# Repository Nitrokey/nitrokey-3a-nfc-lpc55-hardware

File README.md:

# Nitrokey 3A NFC Hardware

The hardware files of [Nitrokey 3A NFC](https://shop.nitrokey.com/shop/nk3an-nitrokey-3a-nfc-147).
The firmware is [here](https://github.com/Nitrokey/nitrokey-3-firmware).

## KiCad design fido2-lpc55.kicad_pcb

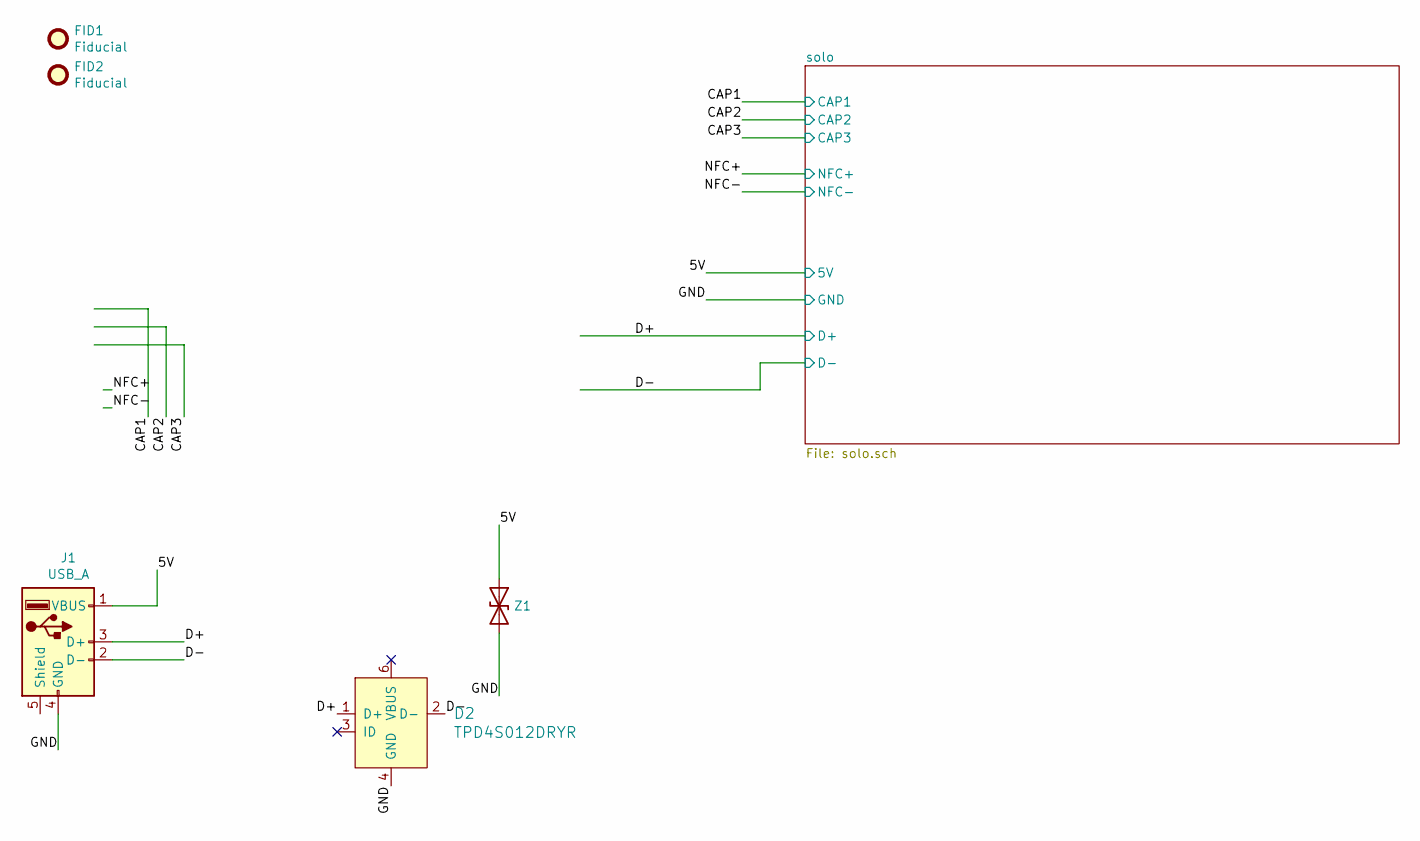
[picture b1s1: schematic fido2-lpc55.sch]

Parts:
D2: TPD4S012DRYR; UFDFN-6_1.45x1mm; MPN TPD4S012DRYR; Digi-Key_PN 296-24244-1-ND
FID1, FID2: Fiducial; Fiducial_0.5mm_Mask1mm
J1: USB_A; USB-A-PLUG
Z1: GG040205100N2P; R_0402_1005Metric; MPN GG040205100N2P

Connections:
/5V: J1.1 (VBUS), Z1.1 (A1); also elsewhere on the board
/D+: D2.1 (D+), J1.3 (D+); also elsewhere on the board
/D-: D2.2 (D-), J1.2 (D-); also elsewhere on the board
GNDREF: D2.4 (GND), J1.4 (GND), Z1.2 (A2); also elsewhere on the board

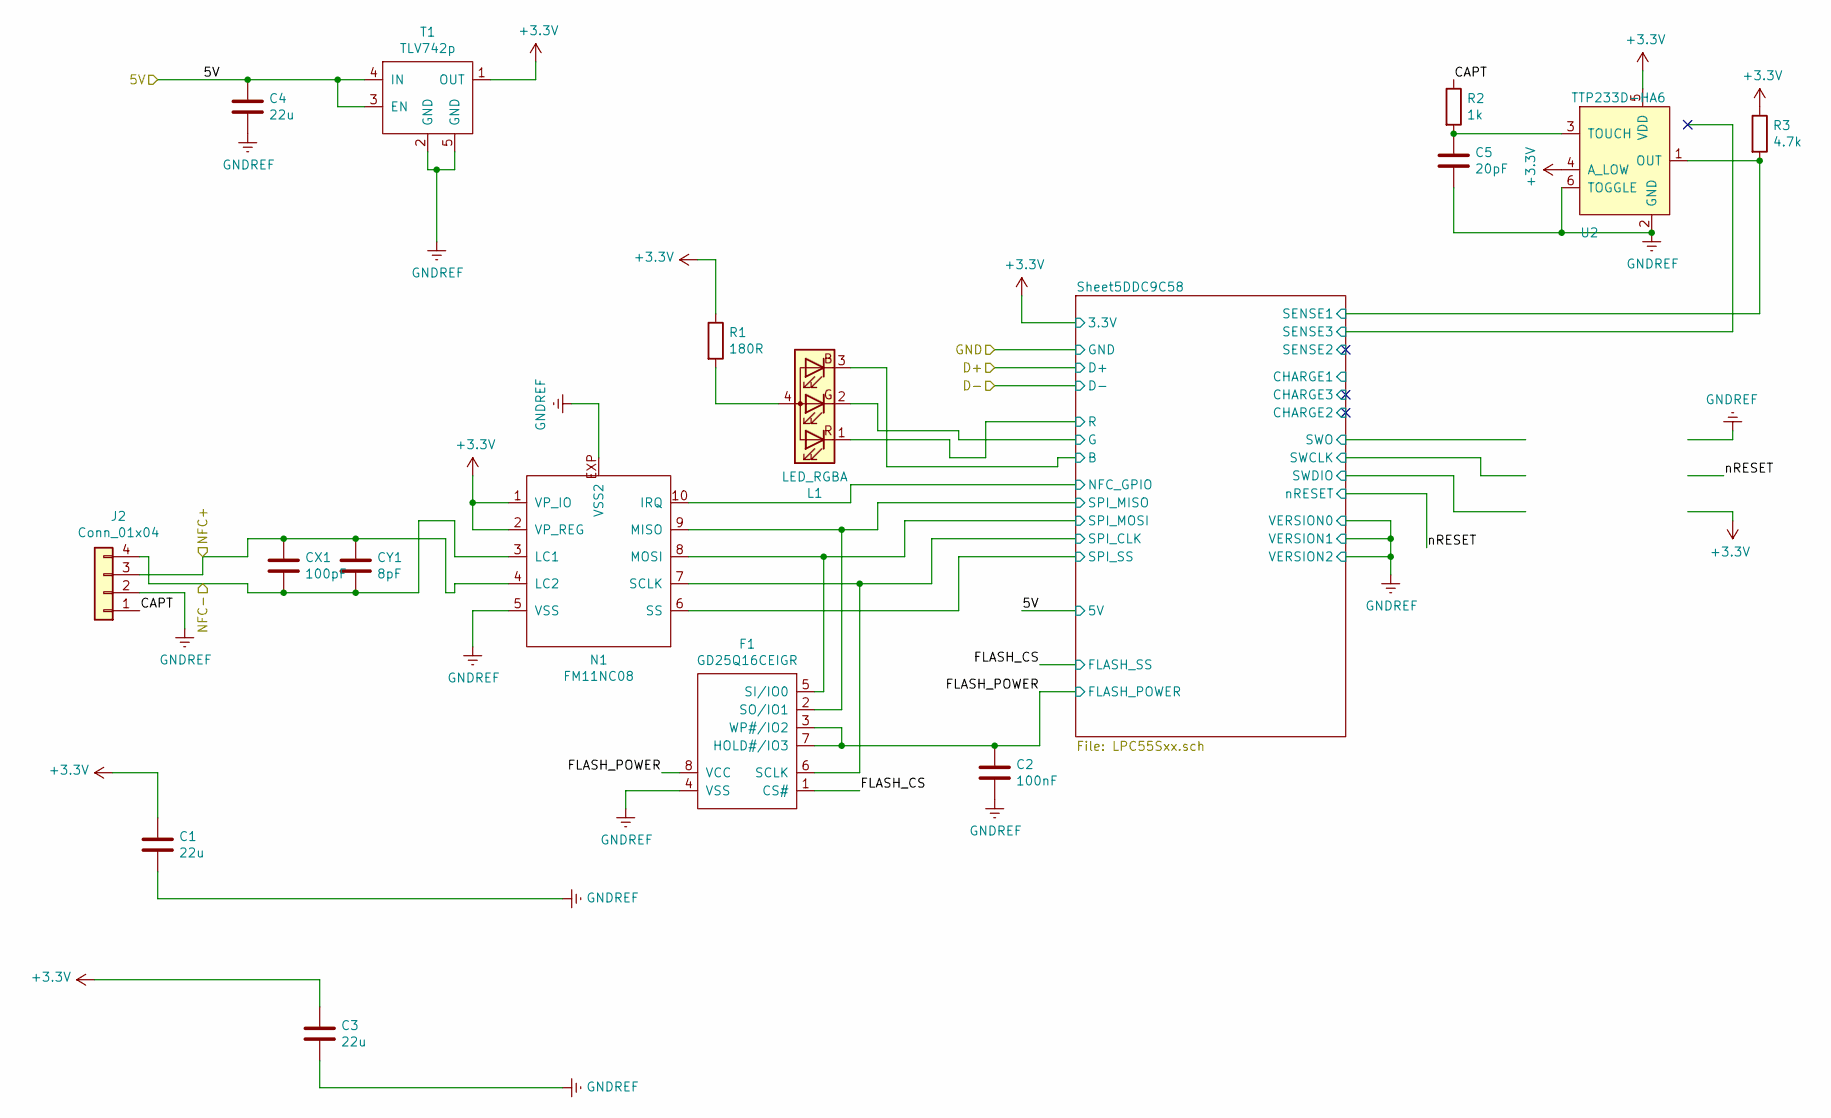
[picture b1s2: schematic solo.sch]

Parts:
C1, C3, C4: 22u; C_0603_1608Metric
C2: 100nF; C_0402_1005Metric
C5: 20pF; C_0402_1005Metric
CX1: 100pF; C_0402_1005Metric
CY1: 8pF; C_0402_1005Metric
F1: GD25Q16CEIGR; FLASH_2x3_USON8; MPN GD25Q16CEIGR
J2: Conn_01x04; FPC_4_0.5-THD0509-04CL-GF
L1: LED_RGBA; RGB_LED_606; MPN EAST1616RGBB4
N1: FM11NC08; DFN-10-1EP_3x3mm_P0.5mm_EP1.55x2.48mm; MPN FM11NC08
R1: 180R; R_0402_1005Metric
R2: 1k; R_0402_1005Metric
R3: 4.7k; R_0402_1005Metric
T1: TLV742p; Texas_X2SON-4_1x1mm_P0.65mm; MPN TLV74233PDQNR
U2: TTP233D-HA6; TSOT-23-6

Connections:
+3V3: C1.1, C3.1, N1.1 (VP_IO), N1.2 (VP_REG), R1.1, R3.1, T1.1 (OUT), U2.4 (A_LOW), U2.5 (VDD); also elsewhere on the board
/5V: C4.1, T1.3 (EN), T1.4 (IN); also elsewhere on the board
/NFC+: CX1.1, CY1.1, J2.3, N1.4 (LC2)
/NFC-: CX1.2, CY1.2, J2.4, N1.3 (LC1)
/solo/CAPT: J2.1, R2.1
/solo/FLASH_CS: F1.1 (CS#); also elsewhere on the board
/solo/FLASH_POWER: C2.1, F1.3 (WP#/IO2), F1.7 (HOLD#/IO3), F1.8 (VCC); also elsewhere on the board
/solo/Sheet5DDC9C58/B: L1.3 (BK); also elsewhere on the board
/solo/Sheet5DDC9C58/G: L1.2 (GK); also elsewhere on the board
/solo/Sheet5DDC9C58/NFC_GPIO: N1.10 (IRQ); also elsewhere on the board
/solo/Sheet5DDC9C58/R: L1.1 (RK); also elsewhere on the board
/solo/Sheet5DDC9C58/SENSE1: R3.2, U2.1 (OUT); also elsewhere on the board
/solo/Sheet5DDC9C58/SPI_CLK: F1.6 (SCLK), N1.7 (SCLK); also elsewhere on the board
/solo/Sheet5DDC9C58/SPI_MISO: F1.2 (SO/IO1), N1.9 (MISO); also elsewhere on the board
/solo/Sheet5DDC9C58/SPI_MOSI: F1.5 (SI/IO0), N1.8 (MOSI); also elsewhere on the board
/solo/Sheet5DDC9C58/SPI_SS: N1.6 (SS); also elsewhere on the board
GNDREF: C1.2, C2.2, C3.2, C4.2, C5.2, F1.4 (VSS), J2.2, N1.5 (VSS), N1.EXP (VSS2), T1.2 (GND), T1.5 (GND), U2.2 (GND), U2.6 (TOGGLE); also elsewhere on the board
unnamed: C5.1, R2.2, U2.3 (TOUCH)
unnamed: L1.4 (A), R1.2

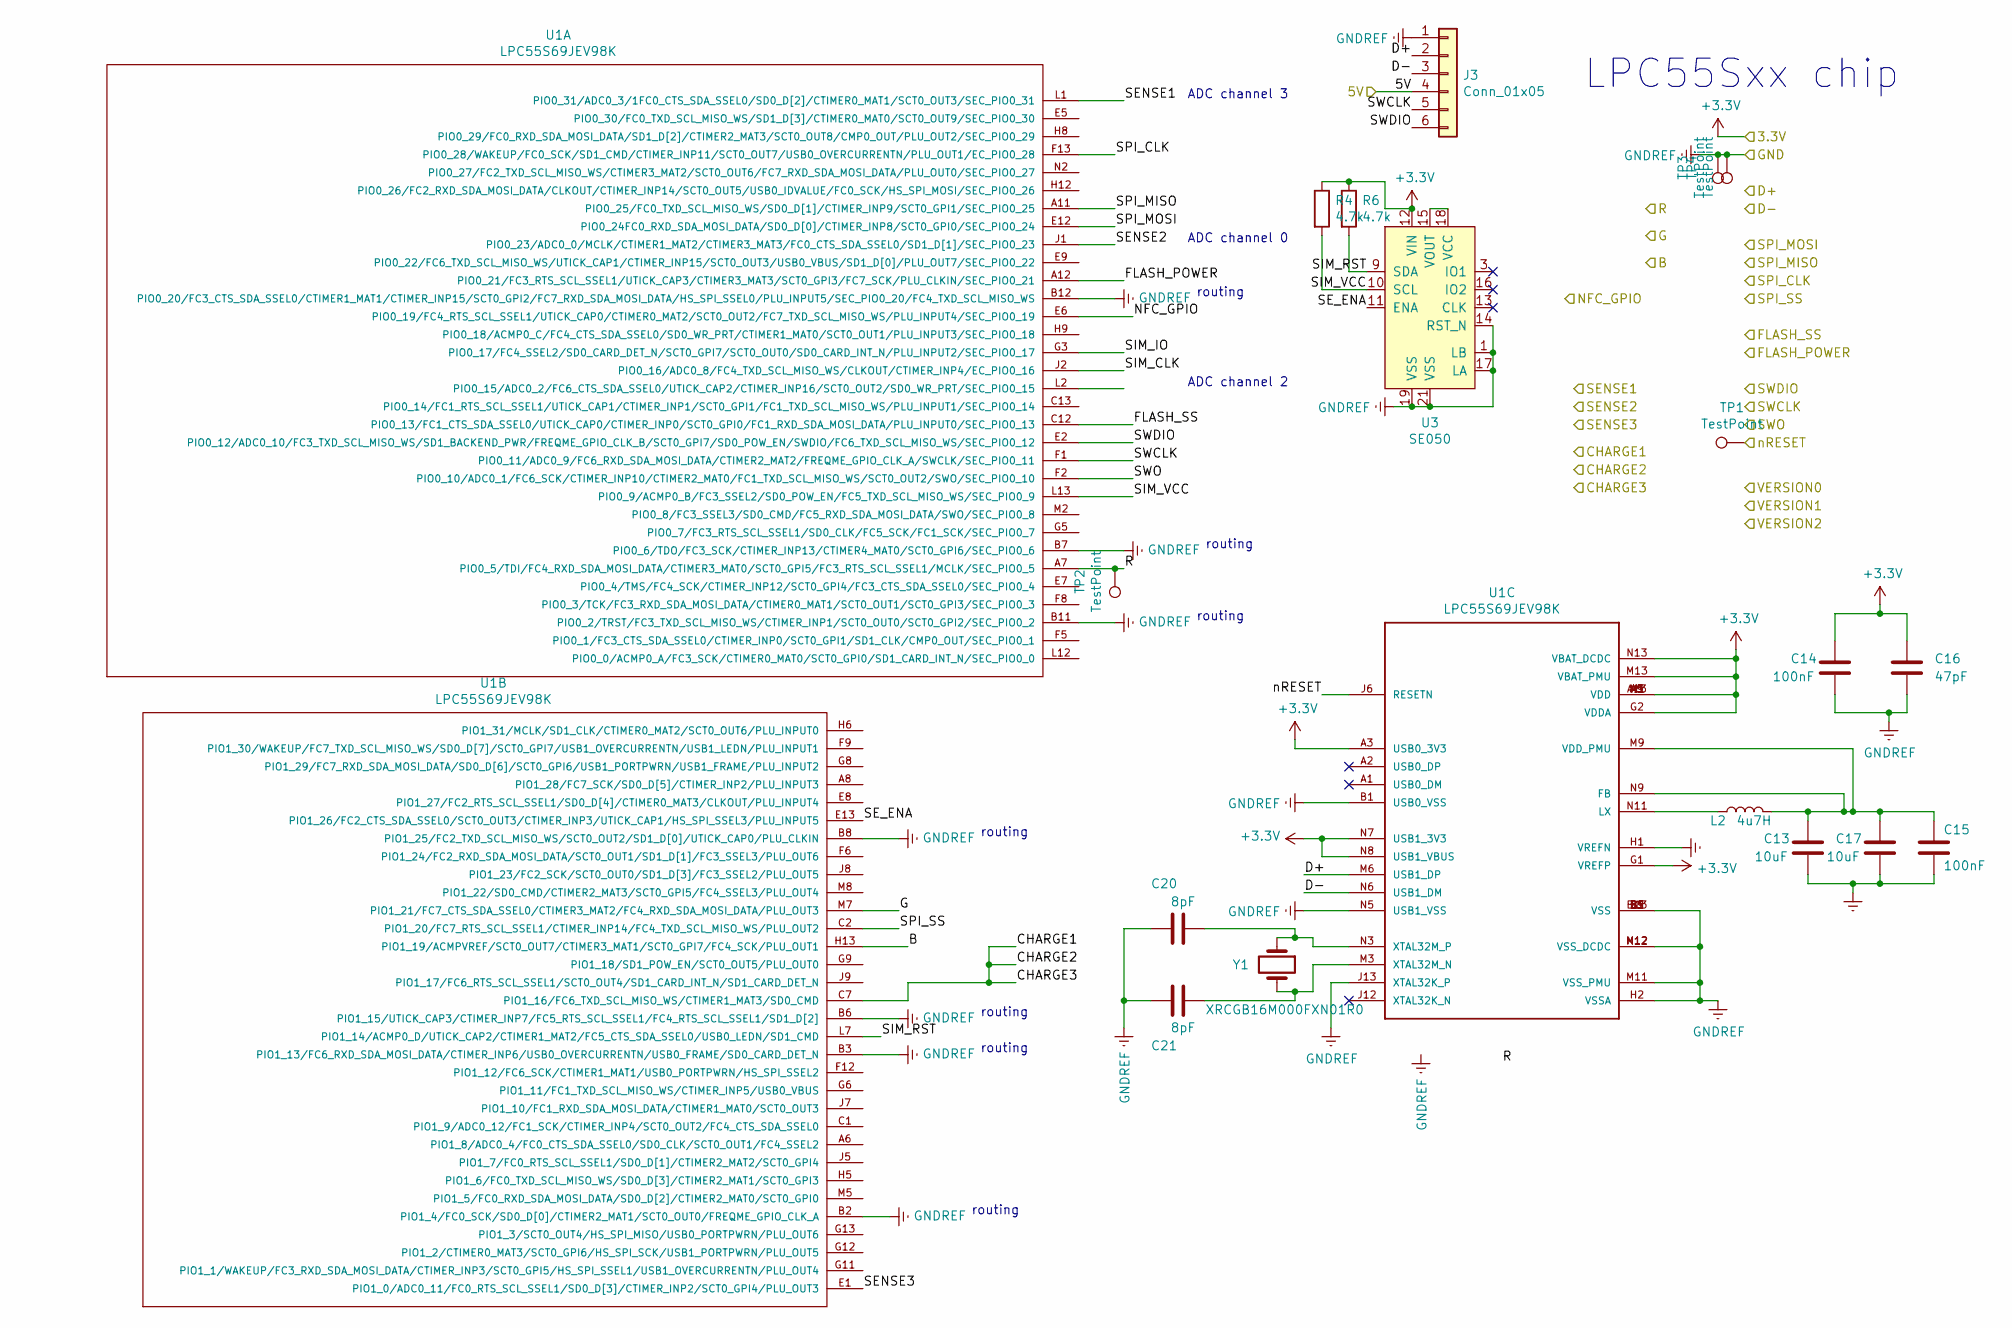
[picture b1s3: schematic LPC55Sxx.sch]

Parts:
C13, C17: 10uF; C_0402_1005Metric
C14, C15: 100nF; C_0402_1005Metric
C16: 47pF; C_0402_1005Metric
C20, C21: 8pF; C_0402_1005Metric
J3: Conn_01x05; nitro_programming_header
L2: 4u7H; L_0603_1608Metric; MPN MLF1608A4R7KTA00
R4, R6: 4.7k; R_0402_1005Metric
TP1, TP2, TP3, TP4: TestPoint; TestPoint_Pad_1.5x1.5mm
U1: LPC55S69JEV98K; BGA98C50P13X13_700X700X97N; MPN LPC55S69JEV98K
U3: SE050; UQFN-20-1EP_3x3mm_P0.4mm_EP1.85x1.85mm
Y1: XRCGB16M000FXN01R0; Crystal-2mmx1.6mm; MPN XRCGB16M000FXN01R0

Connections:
+3V3: C14.1, C16.1, R4.1, R6.1, U1.A3 (USB0_3V3), U1.A5 (VDD), U1.A9 (VDD), U1.A13 (VDD), U1.G1 (VREFP), U1.G2 (VDDA), U1.M1 (VDD), U1.M13 (VBAT_PMU), U1.N7 (USB1_3V3), U1.N8 (USB1_VBUS), U1.N13 (VBAT_DCDC), U3.12 (VIN); also elsewhere on the board
/5V: J3.4; also elsewhere on the board
/D+: J3.2, U1.M6 (USB1_DP); also elsewhere on the board
/D-: J3.3, U1.N6 (USB1_DM); also elsewhere on the board
/solo/FLASH_CS: U1.C12 (PIO0_13/FC1_CTS_SDA_SSEL0/UTICK_CAP0/CT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); also elsewhere on the board
/solo/FLASH_POWER: U1.A12 (PIO0_21/FC3_RTS_SCL_SSEL1/UTICK_CAP3/CT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); also elsewhere on the board
/solo/Sheet5DDC9C58/B: U1.H13 (PIO1_19/ACMPVREF/SCT0_OUT7/CTIMER3_MAT1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); also elsewhere on the board
/solo/Sheet5DDC9C58/CHARGE1: U1.C7 (PIO1_16/FC6_TXD_SCL_MISO_WS/CTIMER1_MAT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)
/solo/Sheet5DDC9C58/G: U1.M7 (PIO1_21/FC7_CTS_SDA_SSEL0/CTIMER3_MAT2/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); also elsewhere on the board
/solo/Sheet5DDC9C58/NFC_GPIO: U1.E6 (PIO0_19/FC4_RTS_SCL_SSEL1/UTICK_CAP0/CT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); also elsewhere on the board
/solo/Sheet5DDC9C58/R: TP2.1, U1.A7 (PIO0_5/TDI/FC4_RXD_SDA_MOSI_DATA/CTIMER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); also elsewhere on the board
/solo/Sheet5DDC9C58/SENSE1: U1.L1 (PIO0_31/ADC0_3/1FC0_CTS_SDA_SSEL0/SD0_D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); also elsewhere on the board
/solo/Sheet5DDC9C58/SENSE2: U1.J1 (PIO0_23/ADC0_0/MCLK/CTIMER1_MAT2/CTIMER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)
/solo/Sheet5DDC9C58/SENSE3: U1.E1 (PIO1_0/ADC0_11/FC0_RTS_SCL_SSEL1/SD0_D[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)
/solo/Sheet5DDC9C58/SE_ENA: U1.E13 (PIO1_26/FC2_CTS_SDA_SSEL0/SCT0_OUT3/CTI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), U3.11 (ENA)
/solo/Sheet5DDC9C58/SIM_CLK: U1.J2 (PIO0_16/ADC0_8/FC4_TXD_SCL_MISO_WS/CLKO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)
/solo/Sheet5DDC9C58/SIM_IO: U1.G3 (PIO0_17/FC4_SSEL2/SD0_CARD_DET_N/SCT0_G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)
/solo/Sheet5DDC9C58/SIM_RST: R6.2, U1.L7 (PIO1_14/ACMP0_D/UTICK_CAP2/CTIMER1_MAT2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), U3.9 (SDA)
/solo/Sheet5DDC9C58/SIM_VCC: R4.2, U1.L13 (PIO0_9/ACMP0_B/FC3_SSEL2/SD0_POW_EN/FC5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), U3.10 (SCL)
/solo/Sheet5DDC9C58/SPI_CLK: U1.F13 (PIO0_28/WAKEUP/FC0_SCK/SD1_CMD/CTIMER_I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); also elsewhere on the board
/solo/Sheet5DDC9C58/SPI_MISO: U1.A11 (PIO0_25/FC0_TXD_SCL_MISO_WS/SD0_D[1]/CT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); also elsewhere on the board
/solo/Sheet5DDC9C58/SPI_MOSI: U1.E12 (PIO0_24FC0_RXD_SDA_MOSI_DATA/SD0_D[0]/C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); also elsewhere on the board
/solo/Sheet5DDC9C58/SPI_SS: U1.C2 (PIO1_20/FC7_RTS_SCL_SSEL1/CTIMER_INP14/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); also elsewhere on the board
/solo/Sheet5DDC9C58/SWCLK: J3.5, U1.F1 (PIO0_11/ADC0_9/FC6_RXD_SDA_MOSI_DATA/CT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)
/solo/Sheet5DDC9C58/SWDIO: J3.6, U1.E2 (PIO0_12/ADC0_10/FC3_TXD_SCL_MISO_WS/SD1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)
/solo/Sheet5DDC9C58/SWO: U1.F2 (PIO0_10/ADC0_1/FC6_SCK/CTIMER_INP10/CTI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)
/solo/nRESET: TP1.1, U1.J6 (RESETN)
GNDREF: C13.2, C14.2, C15.2, C16.2, C17.2, C20.1, C21.1, J3.1, TP3.1, TP4.1, U1.B1 (USB0_VSS), U1.B2 (PIO1_4/FC0_SCK/SD0_D[0]/CTIMER2_MAT1/SC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), U1.B3 (PIO1_13/FC6_RXD_SDA_MOSI_DATA/CTIMER_IN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), U1.B5 (VSS), U1.B6 (PIO1_15/UTICK_CAP3/CTIMER_INP7/FC5_RTS_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), U1.B7 (PIO0_6/TDO/FC3_SCK/CTIMER_INP13/CTIMER4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), U1.B8 (PIO1_25/FC2_TXD_SCL_MISO_WS/SCT0_OUT2/S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), U1.B9 (VSS), U1.B11 (PIO0_2/TRST/FC3_TXD_SCL_MISO_WS/CTIMER_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), U1.B12 (PIO0_20/FC3_CTS_SDA_SSEL0/CTIMER1_MAT1/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), U1.B13 (VSS), U1.H1 (VREFN), U1.H2 (VSSA), U1.J13 (XTAL32K_P), U1.M11 (VSS_PMU), U1.M12 (VSS_DCDC), U1.N1 (VSS), U1.N5 (USB1_VSS), U1.N12 (VSS_DCDC), U3.1 (LB), U3.14 (RST_N), U3.17 (LA), U3.19 (VSS), U3.21 (VSS); also elsewhere on the board
unnamed: C13.1, C15.1, C17.1, L2.2, U1.M9 (VDD_PMU), U1.N9 (FB)
unnamed: C20.2, U1.N3 (XTAL32M_P), Y1.1
unnamed: C21.2, U1.M3 (XTAL32M_N), Y1.2
unnamed: L2.1, U1.N11 (LX)
unnamed: U3.15 (VOUT), U3.18 (VCC)

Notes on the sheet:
LPC55Sxx chip
ADC channel 2
ADC channel 0
routing
ADC channel 3

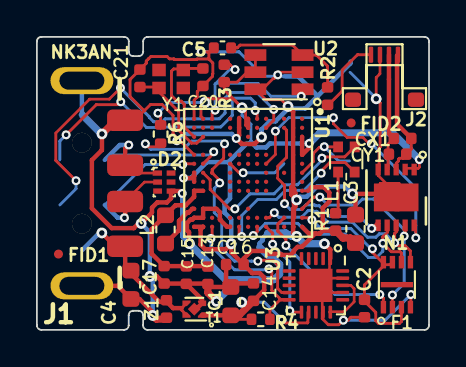
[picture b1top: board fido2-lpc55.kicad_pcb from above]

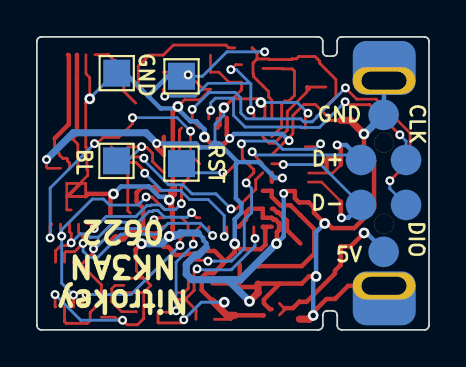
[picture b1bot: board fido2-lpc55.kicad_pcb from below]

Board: 2 copper layers, 21.8 x 16.3 mm, 39 parts (5 on the bottom side), 32 nets.

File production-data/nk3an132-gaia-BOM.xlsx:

BOM Version 2 | NK3AN112 – Gaia | 17.Aug.2022
Component | Description | Part | References | Value | Footprint | Quantity Per PCB | MPN | Manufacturer | Alternative
1 | C0G cap, pref 2%, max 5% | C | C20 C21 CY1 | 8pF | C_0402_1005Metric | 3
2 | C0G cap | C | C16 | 47pF | C_0402_1005Metric | 1
3 | X5R or X7R, 10V | C | C2 C14 C15 | 100n | C_0402_1005Metric | 3
4 | X5R 10V | C | C1 C3 C4 | 22u | C_0603_1608Metric | 3 | C1608X5R1A226M080AC | TDK Corporation
5 | X5R or X7R, 10V | C | C13 C17 | 10uF | C_0402_1005Metric | 2 |  |  | Taiyo Yuden LDK105CBJ106MVLF
6 | C0G cap, pref. 2%, max 5% | C | CX1 | 100pF | C_0402_1005Metric | 1
7 | C0G cap | C | C5 | 20pF | C_0402_1005Metric | 1
8 | Resistor 1% | R | R2 | 1k | R_0402_1005Metric | 1
9 | TVS Diode | tvs diode | D2 | TPD4S012DRYR | UFDFN-6_1.45x1mm | 1 | TPD4S012DRYR | Texas Instruments
10 | SPI flash IC | spi flash | F1 | GD25Q16CEIGR | FLASH_2x3_USON8 | 1 | GD25Q16CEIGR | GigaDevice Semiconductor (HK) Limited
11 | FPC connector 1x4 0.5mm | fpc conn | J2 | Conn_01x04 | FPC_4_0.5-THD0509-04CL-GF | 1 | THD0509-04CL-GF | THD
12 | Inductor | L | L2 | 4u7H | L_0603_1608Metric | 1 | MLF1608A4R7KTA00 | TDK Corporation
13 | RGB LED, red/green/blue/anode | LED_RGBA | L1 | LED_RGBA | RGB_LED_606 | 1 | 150066M153000 | Würth
14 | NFC power harvesting IC | FM11NC08 | N1 | FM11NC08 | MLPD3X3 | 1 | FM11NC08 | Shanghai Fudan Microelectronics Group
15 | USB-A male plug | USB_A_Plug | J1 | USB_A_Plug | USB-A-PLUG | 1 | 480372200 | Molex
16 | Resistor 1% | R | R1 | 180R | R_0402_1005Metric | 1
17 | Resistor 1% | R | R3 R4 R6 | 4.7k | R_0402_1005Metric | 3
18 | 3.3V LDO | TLV742p | T1 | TLV742p | Texas_X2SON-4_1x1mm_P0.65mm | 1 | TLV74233PDQNR | Texas Instruments | Diodes AP7340-33FS4-7
19 | LPC55 microcontroller | LPC55S69JEV98K | U1 | LPC55S69JEV98K | BGA98C50P13X13_700X700X97N | 1 | LPC55S69JEV98K | NXP USA Inc.
20 | Proximity sensor | TTP233D-HA6 | U2 | TTP233 | SOT-23-6 | 1 | TTP233D-HA6 | Tontek Design Tech
21 | Secure element | SE050 | U3 | SE050 | UQFN-20-1EP_3x3mm_P0.4mm_EP1.85x1.85mm | 1 | SE050C1HQ1/Z01SCZ | NXP | SE050C2HQ1/Z01SCZ
22 | Two pin crystal | Crystal | Y1 | XRCGB16M000FXN01R0 | Crystal-2mmx1.6mm | 1 | XRCGB16M000FXN01R0 | Murata
23 | Bidirectional transient-voltage-suppression diode | D_TVS | Z1 | GG040205100N2P | D_0402_1005Metric | 1 | GG040205100N2P | AVX Corporation

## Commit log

2026-04-24 NK3AN132
2026-04-24 add README.md
    Added basic information about Nitrokey 3A NFC hardware and links to firmware.
2026-04-24 add LICENSE.txt
2026-04-24 nk3an133
